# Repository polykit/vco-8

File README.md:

# Polykit Octo VCO aka VCO-8

This repository contains Kicad schematics and PCB layout for an octo 1V/oct VCO. It is based on [this design](https://github.com/polykit/vco-1).

Here you can listen to some short examples how it sounds: [example 1](https://soundcloud.com/polykit/polykit-octo-vco) [example 2](https://soundcloud.com/polykit/polykit-oxcto-vco-2)

# Building instructions

Building it is really straight forward. I suggest starting with components with the lowest height, eg. all SMD components, all diodes, all resistors and so on. Put all of one kind in place at the same time, eg. all 100k resistors. This helps to reduce problems while building it. If you want to try it out it is maybe a good idea to build the [single VCO](https://github.com/polykit/vco-1) version first.

You need either a pair of matched 2N3904s or one BC847BS transistor pair in a SMD package per VCO. I have very good tracking results with the BC847BS and not so good results with the 2N3904s. But maybe this is because of my poor matching. Bend the legs of the NTCs so that they are as close as possbile to the transistors.

## Powering

There are two powering options. First is 16-pin Eurorack with +12V, -12V and +5V. Second one is a 10-pin Eurorack with +12V and -12V and an additional TL431 for precise +5V supply. Make sure to put a jumper to `5V_ALT` and leave out `R3` if you opted for the latter. There is a testpoint `TP` where you can measure while adjusting `TRIM_5V_ALT` to +5.00V. I recommend the second option because of it's precision.

## Tuning

Use the power supply that you are going to use later on for tuning. Otherwise you might need to tune it again. I used a tuning device for this but also a tuning app for your mobile will work just fine. This is how I tuned the oscillators:

* Turn it on and wait at least 15 minutes before you start tuning
* Tune all oscillators roughly to a base note, eg. `C4`. Do this by applying the correct CV input and adjusting the offset trim pot.
* Next is to get the right scale. Start with the first oscillator and adjust scale until you have the correct interval between two notes, eg. your base note `C4` and `D4`. While changing scale overall tuning will change, so go back to your base note from time to time by adjusting the offset. When your are quite close to the correct scale fine tune it for a whole ocatve, eg. using notes `C4` and `C5`. Proceed with the next oscillator.
* Start again with the first oscillator until everything is in tune. Usually you only need to adjust offset for this.

## Tweaks

* Use ferrite beads or just jumpers instead of the 10R resistors for R3, R4 and R5. There is a significant voltage drop over the resistors leading to a lower peak-to-peak amplitude.
* Use 22µ polarized caps instead of 1µ non-polarized ones. The positive side (+) of the cap is torwards the op-amp and negative (-) to the output. I had the impression that it gives you a nicer ramp signal on the output.

## BOM

|Designator|Quantity                                                                                                                                                                                                           |Designation|
|----------|-------------------------------------------------------------------------------------------------------------------------------------------------------------------------------------------------------------------|-----------|
|U1        |1                                                                                                                                                                                                                  |TL431LP*** |
|TRIM_5V_ALT, OFFSET8, OFFSET7, OFFSET6, OFFSET5, OFFSET4, OFFSET3, OFFSET2, OFFSET1|9                                                                                                                                                                                                                  |100k       |
|R197, R36, R180, R156, R132, R108, R84, R60, R12|9                                                                                                                                                                                                                  |47k        |
|R196, R182, R158, R134, R110, R86, R62, R38, R14|9                                                                                                                                                                                                                  |270        |
|C16, C21, C58, C56, C51, C49, C44, C42, C37, C35, C30, C28, C14, C2, C5, C3, C23, C7, C9|19                                                                                                                                                                                                                 |100n       |
|C22, C57, C50, C43, C36, C29, C15, C8|8                                                                                                                                                                                                                  |1n         |
|R50, R195, R194, R171, R170, R147, R146, R123, R122, R99, R98, R75, R74, R51, R27, R26|16                                                                                                                                                                                                                 |1k         |
|R33, R177, R153, R129, R105, R81, R57, R9|8                                                                                                                                                                                                                  |4k7 NTC    |
|T16, T15, T14, T13, T12, T11, T10, T9, T8, T7, T6, T5, T4, T3, T1, T2|16                                                                                                                                                                                                                 |2N3904*    |
|SCALE8, SCALE7, SCALE6, SCALE5, SCALE4, SCALE3, SCALE2, SCALE1|8                                                                                                                                                                                                                  |100        |
|R193, R184, R175, R174, R173, R172, R169, R160, R151, R150, R149, R148, R145, R136, R127, R126, R125, R124, R121, R112, R103, R102, R101, R100, R97, R88, R79, R78, R77, R76, R73, R64, R55, R31, R30, R54, R53, R52, R49, R40, R29, R28, R6, R7, R2, R16, R1, R25|48                                                                                                                                                                                                                 |100k       |
|R192, R186, R176, R168, R162, R152, R144, R138, R128, R120, R114, R104, R96, R90, R80, R72, R66, R56, R32, R48, R42, R24, R8, R18|24                                                                                                                                                                                                                 |4k7        |
|R191, R189, R187, R167, R165, R163, R143, R141, R139, R119, R117, R115, R95, R93, R91, R71, R69, R67, R47, R45, R43, R19, R21, R23|24                                                                                                                                                                                                                 |10k        |
|R190, R166, R142, R118, R94, R70, R46, R22|8                                                                                                                                                                                                                  |2k         |
|R188, R164, R140, R116, R92, R68, R44, R20|8                                                                                                                                                                                                                  |1k8        |
|R185, R161, R137, R113, R89, R65, R41, R17|8                                                                                                                                                                                                                  |470k       |
|R183, R159, R135, R111, R87, R63, R39, R15|8                                                                                                                                                                                                                  |180k       |
|R181, R157, R133, R109, R85, R61, R37, R13|8                                                                                                                                                                                                                  |1M         |
|R179, R155, R131, R107, R83, R59, R35, R11|8                                                                                                                                                                                                                  |100*       |
|R178, R154, R130, R106, R82, R58, R34, R10|8                                                                                                                                                                                                                  |2k2        |
|Q16, Q14, Q12, Q10, Q8, Q6, Q4, Q2|8                                                                                                                                                                                                                  |BS170      |
|Q15, Q13, Q11, Q9, Q7, Q5, Q3, Q1|8                                                                                                                                                                                                                  |BC847BS*   |
|IC16, IC14, IC12, IC10, IC8, IC6, IC2, IC4|8                                                                                                                                                                                                                  |TL072P     |
|IC15, IC13, IC11, IC9, IC7, IC5, IC1, IC3|8                                                                                                                                                                                                                  |TL074P     |
|D16, D15, D14, D13, D12, D11, D10, D9, D8, D7, D6, D5, D4, D3, D2, D1|16                                                                                                                                                                                                                 |1N4148     |
|C62, C55, C48, C41, C34, C27, C20, C13|8                                                                                                                                                                                                                  |10n        |
|C61, C54, C47, C40, C33, C19, C26, C12|8                                                                                                                                                                                                                  |1µ**         |
|C60, C53, C46, C39, C32, C18, C25, C11|8                                                                                                                                                                                                                  |100p**       |
|C59, C52, C45, C38, C31, C17, C24, C10|8                                                                                                                                                                                                                  |1n**       |
|C6, C4, C1  |3                                                                                                                                                                                                                  |10µ polarized       |
|R4, R5, R3  |3                                                                                                                                                                                                                  |10         |
|PWR1      |1                                                                                                                                                                                                                  |ML16 or ML10***|                                                                                           

\* Use either matched pairs of 2N3904s or BC847BS dual transistors. Use 120R instead of 100R for R179, R155, R131, R107, R83, R59, R35 and R11 when you are going for the 2N3904s.

\** Use polypropylene or similar caps

\*** See powering options. Leave out U1, R196, R197 and TRIM_5V_ALT if you opted for 16-pin Eurorack supply with +5V in place.

# References

https://github.com/polykit/vco-1

https://www.diodes.com/assets/Datasheets/ds30222.pdf

https://www.ti.com/lit/ds/symlink/tl431.pdf

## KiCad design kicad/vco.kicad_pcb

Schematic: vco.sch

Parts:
C1, C4, C6: 47µ; E2,5-5
C2, C3, C5: 100n; C050-030X075
PWR1: ML16
R3, R4, R5: 10; 0207_7
R196: 270; 0207_7
R197: 47k; 0207_7
TP1: Conn_01x01; 1X01
TRIM_5V1: 100k; S64YW
U1: TL431LP; TO-92_Inline

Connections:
5V_ALT: R196.2, R197.1, TP1.1, U1.3 (K); also elsewhere on the board
+5V: C1.+, C3.2, R3.1; also elsewhere on the board
+12V: C5.2, C6.+, R4.1, R196.1; also elsewhere on the board
-12V: C2.2, C4.-, R5.1; also elsewhere on the board
GND: C1.-, C2.1, C3.1, C4.+, C5.1, C6.-, PWR1.3, PWR1.4, PWR1.5, PWR1.6, PWR1.7, PWR1.8, TRIM_5V1.E, TRIM_5V1.S, U1.2 (A); also elsewhere on the board
unnamed: PWR1.1, PWR1.2, R5.2
unnamed: PWR1.9, PWR1.10, R4.2
unnamed: PWR1.11, PWR1.12, R3.2
unnamed: R197.2, TRIM_5V1.A, U1.1 (REF)

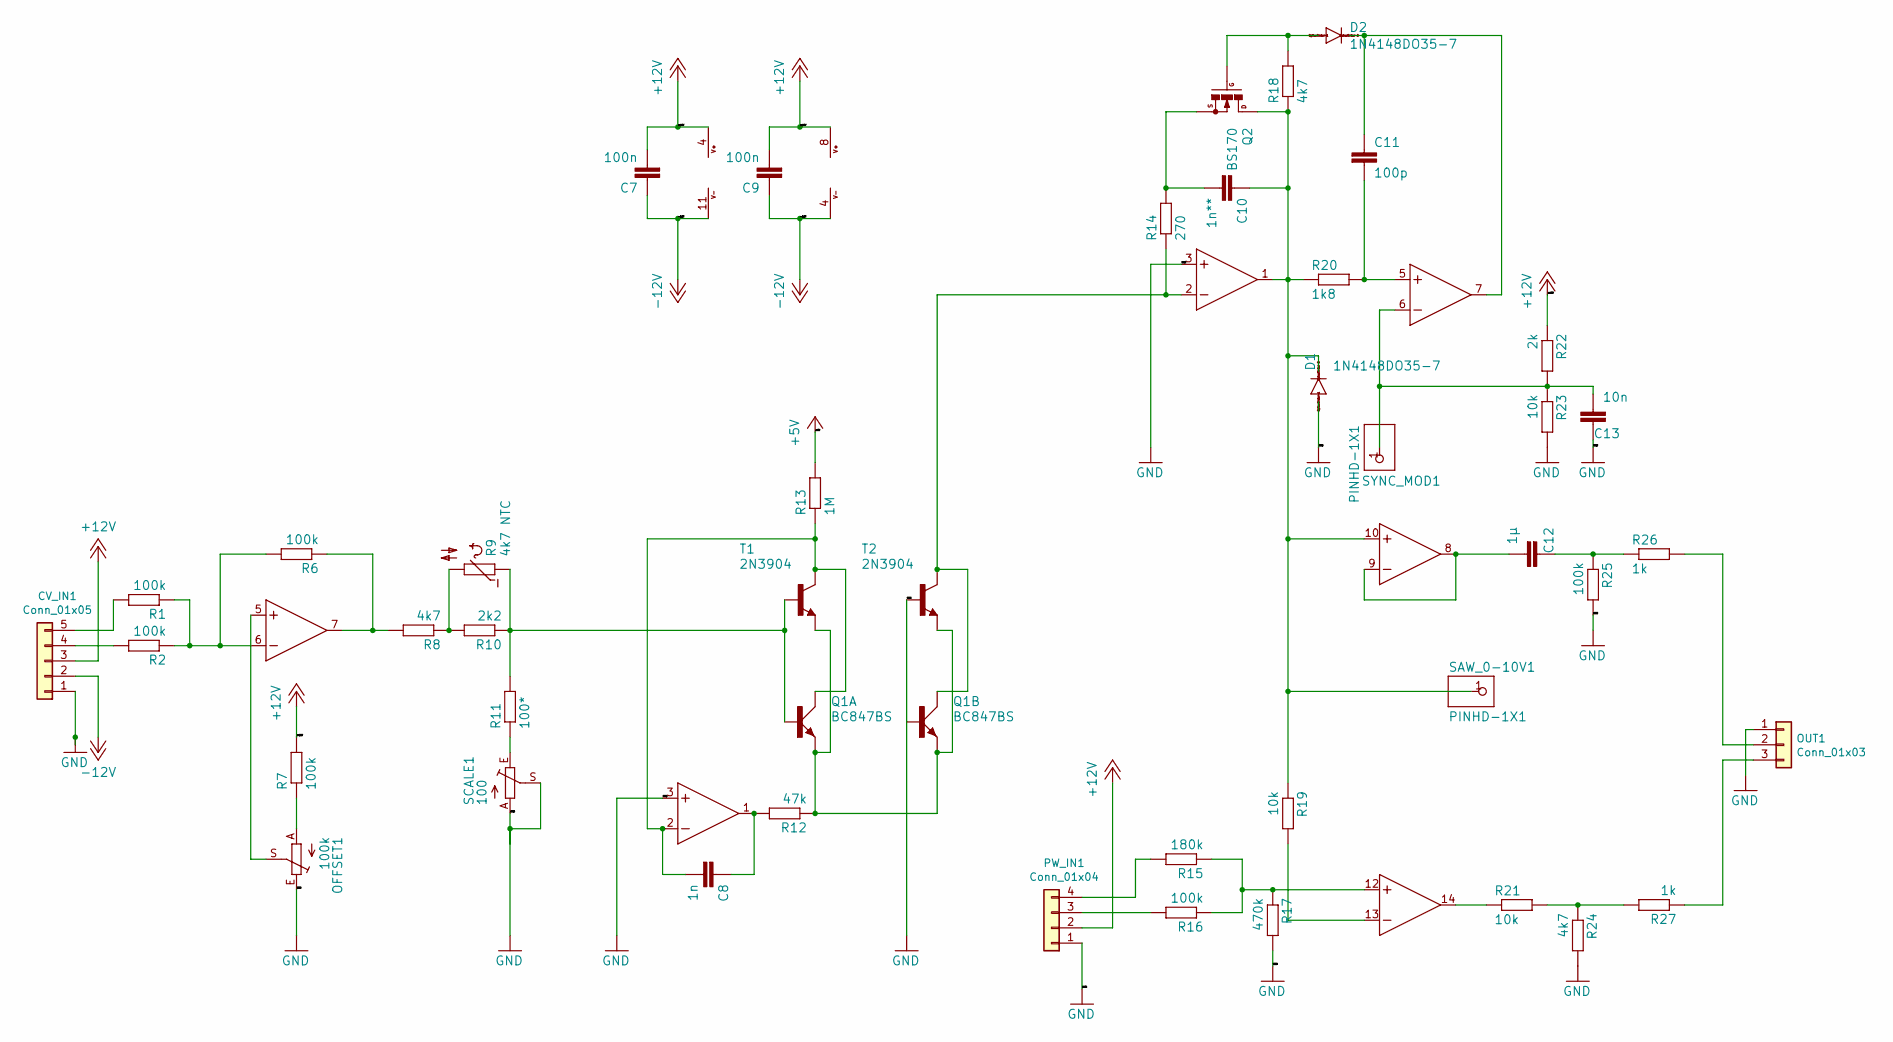
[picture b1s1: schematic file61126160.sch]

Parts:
C7, C9: 100n; C050-030X075
C8: 1n; C050-024X044
C10: 1n**; C050-030X075
C11: 100p; C050-030X075
C12: 1µ; C050-030X075
C13: 10n; C050-030X075
CV_IN1: Conn_01x05; Molex_KK-254_AE-6410-05A_1x05_P2.54mm_Vertical
D1, D2: 1N4148DO35-7; DO35-7
IC1: TL074P; DIL14
IC2: TL072P; DIL08
OFFSET1: 100k; S64YW
OUT1: Conn_01x03; Molex_KK-254_AE-6410-03A_1x03_P2.54mm_Vertical
PW_IN1: Conn_01x04; Molex_KK-254_AE-6410-04A_1x04_P2.54mm_Vertical
Q1: BC847BS; SOT363_PHILIPS
Q2: BS170; SOT54E
R1, R2, R6, R7, R16, R25: 100k; 0207_7
R8, R18, R24: 4k7; 0207_7
R9: 4k7 NTC; P640
R10: 2k2; 0207_7
R11: 100*; 0207_7
R12: 47k; 0207_7
R13: 1M; 0207_7
R14: 270; 0207_7
R15: 180k; 0207_7
R17: 470k; 0207_7
R19, R21, R23: 10k; 0207_7
R20: 1k8; 0207_7
R22: 2k; 0207_7
R26, R27: 1k; 0207_7
SAW_0-10V1: PINHD-1X1; 1X01
SCALE1: 100; S64YW
SYNC_MOD1: PINHD-1X1; 1X01
T1, T2: 2N3904; TO92

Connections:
+5V: R13.2; also elsewhere on the board
+12V: C7.2, C9.2, CV_IN1.3, IC1.4 (V+), IC2.8 (V+), PW_IN1.2, R7.2, R22.1; also elsewhere on the board
-12V: C7.1, C9.1, CV_IN1.2, IC1.11 (V-), IC2.4 (V-); also elsewhere on the board
GND: C13.1, CV_IN1.1, D1.A, IC1.3 (+IN), IC2.3 (+IN), OFFSET1.E, OUT1.1, PW_IN1.1, Q1.5 (B), R17.2, R23.2, R24.2, R25.2, SCALE1.A, SCALE1.S, T2.2 (B); also elsewhere on the board
unnamed: C8.1, IC1.1 (OUT), R12.2
unnamed: C8.2, IC1.2 (-IN), Q1.6 (C), R13.1, T1.1 (C)
unnamed: C10.1, D1.C, IC1.10 (+IN), IC2.1 (OUT), Q2.D, R18.1, R19.1, R20.1, SAW_0-10V1.1
unnamed: C10.2, Q2.S, R14.2
unnamed: C11.1, D2.C, IC2.7 (OUT)
unnamed: C11.2, IC2.5 (+IN), R20.2
unnamed: C12.1, R25.1, R26.1
unnamed: C12.2, IC1.8 (OUT), IC1.9 (-IN)
unnamed: C13.2, IC2.6 (-IN), R22.2, R23.1, SYNC_MOD1.1
unnamed: CV_IN1.4, R2.2
unnamed: CV_IN1.5, R1.2
unnamed: D2.A, Q2.G, R18.2
unnamed: IC1.5 (+IN), OFFSET1.S
unnamed: IC1.6 (-IN), R1.1, R2.1, R6.2
unnamed: IC1.7 (OUT), R6.1, R8.2
unnamed: IC1.12 (+IN), R15.1, R16.1, R17.1
unnamed: IC1.13 (-IN), R19.2
unnamed: IC1.14 (OUT), R21.1
unnamed: IC2.2 (-IN), Q1.3 (C), R14.1, T2.1 (C)
unnamed: OFFSET1.A, R7.1
unnamed: OUT1.2, R26.2
unnamed: OUT1.3, R27.1
unnamed: PW_IN1.3, R16.2
unnamed: PW_IN1.4, R15.2
unnamed: Q1.1 (E), Q1.4 (E), R12.1, T1.3 (E), T2.3 (E)
unnamed: Q1.2 (B), R9.1, R10.1, R11.2, T1.2 (B)
unnamed: R8.1, R9.2, R10.2
unnamed: R11.1, SCALE1.E
unnamed: R21.2, R24.1, R27.2

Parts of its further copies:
C14, C16, C21, C23, C28, C30, C35, C37, C42, C44, C49, C51, C56, C58: 100n; C050-030X075
C15, C29, C36, C43, C50, C57: 1n; C050-024X044
C17, C24, C31, C38, C45, C52, C59: 1n**; C050-030X075
C18, C25, C32, C39, C46, C53, C60: 100p; C050-030X075
C19, C33, C40, C47, C54, C61: 1µ; C050-030X075
C27, C34, C41, C48, C55, C62: 10n; C050-030X075
CV_IN2, CV_IN3, CV_IN4, CV_IN5, CV_IN6, CV_IN7, CV_IN8: Conn_01x05; Molex_KK-254_AE-6410-05A_1x05_P2.54mm_Vertical
D3, D4, D5, D6, D7, D8, D9, D10, D11, D12, D13, D14, D15, D16: 1N4148DO35-7; DO35-7
IC3, IC5, IC7, IC9, IC11, IC13, IC15: TL074P; DIL14
IC4, IC6, IC8, IC10, IC12, IC14, IC16: TL072P; DIL08
OFFSET2, OFFSET3, OFFSET4, OFFSET5, OFFSET6, OFFSET7, OFFSET8: 100k; S64YW
OUT2, OUT3, OUT4, OUT5, OUT6, OUT7, OUT8: Conn_01x03; Molex_KK-254_AE-6410-03A_1x03_P2.54mm_Vertical
PW_IN2, PW_IN3, PW_IN4, PW_IN5, PW_IN6, PW_IN7, PW_IN8: Conn_01x04; Molex_KK-254_AE-6410-04A_1x04_P2.54mm_Vertical
Q3, Q5, Q7, Q9, Q11, Q13, Q15: BC847BS; SOT363_PHILIPS
Q4, Q6, Q8, Q10, Q12, Q14, Q16: BS170; SOT54E
R28, R29, R30, R31, R52, R53, R55, R64, R73, R76, R77, R78, R79, R88, R97, R100, R101, R102, R103, R112, R121, R124, R125, R126, R127, R136, R145, R148, R149, R150, R151, R160, R169, R172, R173, R174, R175, R184, R193: 100k; 0207_7
R32, R56, R66, R72, R80, R90, R96, R104, R114, R120, R128, R138, R144, R152, R162, R168, R176, R186, R192: 4k7; 0207_7
R33, R57, R81, R105, R129, R153, R177: 4k7 NTC; P640
R34, R58, R82, R106, R130, R154, R178: 2k2; 0207_7
R37, R61, R85, R109, R133, R157, R181: 1M; 0207_7
R38, R62, R86, R110, R134, R158, R182: 270; 0207_7
R39, R63, R87, R111, R135, R159, R183: 180k; 0207_7
R43, R45, R67, R69, R71, R91, R93, R95, R115, R117, R119, R139, R141, R143, R163, R165, R167, R187, R189, R191: 10k; 0207_7
R44, R68, R92, R116, R140, R164, R188: 1k8; 0207_7
R50, R51, R74, R75, R98, R99, R122, R123, R146, R147, R170, R171, R194, R195: 1k; 0207_7
R59, R83, R107, R131, R155, R179: 100*; 0207_7
R60, R84, R108, R132, R156, R180: 47k; 0207_7
R65, R89, R113, R137, R161, R185: 470k; 0207_7
R70, R94, R118, R142, R166, R190: 2k; 0207_7
SAW_0-10V2, SAW_0-10V3, SAW_0-10V4, SAW_0-10V5, SAW_0-10V6, SAW_0-10V7, SAW_0-10V8: PINHD-1X1; 1X01
SCALE2, SCALE3, SCALE4, SCALE5, SCALE6, SCALE7, SCALE8: 100; S64YW
SYNC_MOD2, SYNC_MOD3, SYNC_MOD4, SYNC_MOD5, SYNC_MOD6, SYNC_MOD7, SYNC_MOD8: PINHD-1X1; 1X01
T3, T4, T5, T6, T7, T8, T9, T10, T11, T12, T13, T14, T15, T16: 2N3904; TO92

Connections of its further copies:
+5V: R37.2, R61.2, R85.2, R109.2, R133.2, R157.2, R181.2; also elsewhere on the board
+12V: C14.2, C16.2, C21.2, C23.2, C28.2, C30.2, C35.2, C37.2, C42.2, C44.2, C49.2, C51.2, C56.2, C58.2, CV_IN2.3, CV_IN3.3, CV_IN4.3, CV_IN5.3, CV_IN6.3, CV_IN7.3, CV_IN8.3, IC3.4 (V+), IC4.8 (V+), IC5.4 (V+), IC6.8 (V+), IC7.4 (V+), IC8.8 (V+), IC9.4 (V+), IC10.8 (V+), IC11.4 (V+), IC12.8 (V+), IC13.4 (V+), IC14.8 (V+), IC15.4 (V+), IC16.8 (V+), PW_IN2.2, PW_IN3.2, PW_IN4.2, PW_IN5.2, PW_IN6.2, PW_IN7.2, PW_IN8.2, R31.2, R55.2, R70.1, R79.2, R94.1, R103.2, R118.1, R127.2, R142.1, R151.2, R166.1, R175.2, R190.1; also elsewhere on the board
-12V: C14.1, C16.1, C21.1, C23.1, C28.1, C30.1, C35.1, C37.1, C42.1, C44.1, C49.1, C51.1, C56.1, C58.1, CV_IN2.2, CV_IN3.2, CV_IN4.2, CV_IN5.2, CV_IN6.2, CV_IN7.2, CV_IN8.2, IC3.11 (V-), IC4.4 (V-), IC5.11 (V-), IC6.4 (V-), IC7.11 (V-), IC8.4 (V-), IC9.11 (V-), IC10.4 (V-), IC11.11 (V-), IC12.4 (V-), IC13.11 (V-), IC14.4 (V-), IC15.11 (V-), IC16.4 (V-); also elsewhere on the board
GND: C27.1, C34.1, C41.1, C48.1, C55.1, C62.1, CV_IN2.1, CV_IN3.1, CV_IN4.1, CV_IN5.1, CV_IN6.1, CV_IN7.1, CV_IN8.1, D3.A, D5.A, D7.A, D9.A, D11.A, D13.A, D15.A, IC3.3 (+IN), IC4.3 (+IN), IC5.3 (+IN), IC6.3 (+IN), IC7.3 (+IN), IC8.3 (+IN), IC9.3 (+IN), IC10.3 (+IN), IC11.3 (+IN), IC12.3 (+IN), IC13.3 (+IN), IC14.3 (+IN), IC15.3 (+IN), IC16.3 (+IN), OFFSET2.E, OFFSET3.E, OFFSET4.E, OFFSET5.E, OFFSET6.E, OFFSET7.E, OFFSET8.E, OUT2.1, OUT3.1, OUT4.1, OUT5.1, OUT6.1, OUT7.1, OUT8.1, PW_IN2.1, PW_IN3.1, PW_IN4.1, PW_IN5.1, PW_IN6.1, PW_IN7.1, PW_IN8.1, Q3.5 (B), Q5.5 (B), Q7.5 (B), Q9.5 (B), Q11.5 (B), Q13.5 (B), Q15.5 (B), R65.2, R71.2, R72.2, R73.2, R89.2, R95.2, R96.2, R97.2, R113.2, R119.2, R120.2, R121.2, R137.2, R143.2, R144.2, R145.2, R161.2, R167.2, R168.2, R169.2, R185.2, R191.2, R192.2, R193.2, SCALE2.A, SCALE2.S, SCALE3.A, SCALE3.S, SCALE4.A, SCALE4.S, SCALE5.A, SCALE5.S, SCALE6.A, SCALE6.S, SCALE7.A, SCALE7.S, SCALE8.A, SCALE8.S, T4.2 (B), T6.2 (B), T8.2 (B), T10.2 (B), T12.2 (B), T14.2 (B), T16.2 (B); also elsewhere on the board
unnamed 14: C15.1, IC3.1 (OUT); also elsewhere on the board
unnamed: C15.2, IC3.2 (-IN), Q3.6 (C), R37.1, T3.1 (C)
unnamed 16: C17.1, D3.C, IC3.10 (+IN), IC4.1 (OUT), Q4.D, R43.1, R44.1, SAW_0-10V2.1; also elsewhere on the board
unnamed: C17.2, Q4.S, R38.2
unnamed: C18.1, D4.C, IC4.7 (OUT)
unnamed: C18.2, IC4.5 (+IN), R44.2
unnamed 20: C19.1, R50.1; also elsewhere on the board
unnamed: C19.2, IC3.8 (OUT), IC3.9 (-IN)
unnamed 22: IC4.6 (-IN), SYNC_MOD2.1; also elsewhere on the board
unnamed 23: IC5.1 (OUT), R60.2; also elsewhere on the board
unnamed 24: IC5.2 (-IN), Q5.6 (C), R61.1, T5.1 (C); also elsewhere on the board
unnamed: C24.1, D5.C, IC5.10 (+IN), IC6.1 (OUT), Q6.D, R66.1, R67.1, R68.1, SAW_0-10V3.1
unnamed: C24.2, Q6.S, R62.2
unnamed: C25.1, D6.C, IC6.7 (OUT)
unnamed: C25.2, IC6.5 (+IN), R68.2
unnamed 29: R73.1, R74.1; also elsewhere on the board
unnamed 30: IC5.8 (OUT), IC5.9 (-IN); also elsewhere on the board
unnamed: C27.2, IC6.6 (-IN), R70.2, R71.1, SYNC_MOD3.1
unnamed: C29.1, IC7.1 (OUT), R84.2
unnamed: C29.2, IC7.2 (-IN), Q7.6 (C), R85.1, T7.1 (C)
unnamed: C31.1, D7.C, IC7.10 (+IN), IC8.1 (OUT), Q8.D, R90.1, R91.1, R92.1, SAW_0-10V4.1
unnamed: C31.2, Q8.S, R86.2
unnamed: C32.1, D8.C, IC8.7 (OUT)
unnamed: C32.2, IC8.5 (+IN), R92.2
unnamed: C33.1, R97.1, R98.1
unnamed: C33.2, IC7.8 (OUT), IC7.9 (-IN)
unnamed: C34.2, IC8.6 (-IN), R94.2, R95.1, SYNC_MOD4.1
unnamed: C36.1, IC9.1 (OUT), R108.2
unnamed: C36.2, IC9.2 (-IN), Q9.6 (C), R109.1, T9.1 (C)
unnamed: C38.1, D9.C, IC9.10 (+IN), IC10.1 (OUT), Q10.D, R114.1, R115.1, R116.1, SAW_0-10V5.1
unnamed: C38.2, Q10.S, R110.2
unnamed: C39.1, D10.C, IC10.7 (OUT)
unnamed: C39.2, IC10.5 (+IN), R116.2
unnamed: C40.1, R121.1, R122.1
unnamed: C40.2, IC9.8 (OUT), IC9.9 (-IN)
unnamed: C41.2, IC10.6 (-IN), R118.2, R119.1, SYNC_MOD5.1
unnamed: C43.1, IC11.1 (OUT), R132.2
unnamed: C43.2, IC11.2 (-IN), Q11.6 (C), R133.1, T11.1 (C)
unnamed: C45.1, D11.C, IC11.10 (+IN), IC12.1 (OUT), Q12.D, R138.1, R139.1, R140.1, SAW_0-10V6.1
unnamed: C45.2, Q12.S, R134.2
unnamed: C46.1, D12.C, IC12.7 (OUT)
unnamed: C46.2, IC12.5 (+IN), R140.2
unnamed: C47.1, R145.1, R146.1
unnamed: C47.2, IC11.8 (OUT), IC11.9 (-IN)
unnamed: C48.2, IC12.6 (-IN), R142.2, R143.1, SYNC_MOD6.1
unnamed: C50.1, IC13.1 (OUT), R156.2
unnamed: C50.2, IC13.2 (-IN), Q13.6 (C), R157.1, T13.1 (C)
unnamed: C52.1, D13.C, IC13.10 (+IN), IC14.1 (OUT), Q14.D, R162.1, R163.1, R164.1, SAW_0-10V7.1
unnamed: C52.2, Q14.S, R158.2
unnamed: C53.1, D14.C, IC14.7 (OUT)
unnamed: C53.2, IC14.5 (+IN), R164.2
unnamed: C54.1, R169.1, R170.1
unnamed: C54.2, IC13.8 (OUT), IC13.9 (-IN)
unnamed: C55.2, IC14.6 (-IN), R166.2, R167.1, SYNC_MOD7.1
unnamed: C57.1, IC15.1 (OUT), R180.2
unnamed: C57.2, IC15.2 (-IN), Q15.6 (C), R181.1, T15.1 (C)
unnamed: C59.1, D15.C, IC15.10 (+IN), IC16.1 (OUT), Q16.D, R186.1, R187.1, R188.1, SAW_0-10V8.1
unnamed: C59.2, Q16.S, R182.2
unnamed: C60.1, D16.C, IC16.7 (OUT)
unnamed: C60.2, IC16.5 (+IN), R188.2
unnamed: C61.1, R193.1, R194.1
unnamed: C61.2, IC15.8 (OUT), IC15.9 (-IN)
unnamed: C62.2, IC16.6 (-IN), R190.2, R191.1, SYNC_MOD8.1
unnamed: CV_IN2.4, R29.2
unnamed: CV_IN2.5, R28.2
unnamed: CV_IN3.4, R53.2
unnamed: CV_IN3.5, R52.2
unnamed: CV_IN4.4, R77.2
unnamed: CV_IN4.5, R76.2
unnamed: CV_IN5.4, R101.2
unnamed: CV_IN5.5, R100.2
unnamed: CV_IN6.4, R125.2
unnamed: CV_IN6.5, R124.2
unnamed: CV_IN7.4, R149.2
unnamed: CV_IN7.5, R148.2
unnamed: CV_IN8.4, R173.2
unnamed: CV_IN8.5, R172.2
unnamed 94: D4.A, Q4.G; also elsewhere on the board
unnamed: D6.A, Q6.G, R66.2
unnamed: D8.A, Q8.G, R90.2
unnamed: D10.A, Q10.G, R114.2
unnamed: D12.A, Q12.G, R138.2
unnamed: D14.A, Q14.G, R162.2
unnamed: D16.A, Q16.G, R186.2
unnamed: IC3.5 (+IN), OFFSET2.S
unnamed: IC3.6 (-IN), R28.1, R29.1, R30.2
unnamed: IC3.7 (OUT), R30.1, R32.2
unnamed 111: IC3.12 (+IN), R39.1; also elsewhere on the board
unnamed: IC3.13 (-IN), R43.2
unnamed: IC3.14 (OUT), R45.1
unnamed: IC4.2 (-IN), Q3.3 (C), R38.1, T4.1 (C)
unnamed: IC5.5 (+IN), OFFSET3.S
unnamed 116: IC5.6 (-IN), R52.1, R53.1; also elsewhere on the board
unnamed 117: IC5.7 (OUT), R56.2; also elsewhere on the board
unnamed: IC5.12 (+IN), R63.1, R64.1, R65.1
unnamed: IC5.13 (-IN), R67.2
unnamed: IC5.14 (OUT), R69.1
unnamed: IC6.2 (-IN), Q5.3 (C), R62.1, T6.1 (C)
unnamed: IC7.5 (+IN), OFFSET4.S
unnamed: IC7.6 (-IN), R76.1, R77.1, R78.2
unnamed: IC7.7 (OUT), R78.1, R80.2
unnamed: IC7.12 (+IN), R87.1, R88.1, R89.1
unnamed: IC7.13 (-IN), R91.2
unnamed: IC7.14 (OUT), R93.1
unnamed: IC8.2 (-IN), Q7.3 (C), R86.1, T8.1 (C)
unnamed: IC9.5 (+IN), OFFSET5.S
unnamed: IC9.6 (-IN), R100.1, R101.1, R102.2
unnamed: IC9.7 (OUT), R102.1, R104.2
unnamed: IC9.12 (+IN), R111.1, R112.1, R113.1
unnamed: IC9.13 (-IN), R115.2
unnamed: IC9.14 (OUT), R117.1
unnamed: IC10.2 (-IN), Q9.3 (C), R110.1, T10.1 (C)
unnamed: IC11.5 (+IN), OFFSET6.S
unnamed: IC11.6 (-IN), R124.1, R125.1, R126.2
unnamed: IC11.7 (OUT), R126.1, R128.2
unnamed: IC11.12 (+IN), R135.1, R136.1, R137.1
unnamed: IC11.13 (-IN), R139.2
unnamed: IC11.14 (OUT), R141.1
unnamed: IC12.2 (-IN), Q11.3 (C), R134.1, T12.1 (C)
unnamed: IC13.5 (+IN), OFFSET7.S
unnamed: IC13.6 (-IN), R148.1, R149.1, R150.2
unnamed: IC13.7 (OUT), R150.1, R152.2
unnamed: IC13.12 (+IN), R159.1, R160.1, R161.1
unnamed: IC13.13 (-IN), R163.2
unnamed: IC13.14 (OUT), R165.1
unnamed: IC14.2 (-IN), Q13.3 (C), R158.1, T14.1 (C)
unnamed: IC15.5 (+IN), OFFSET8.S
unnamed: IC15.6 (-IN), R172.1, R173.1, R174.2
unnamed: IC15.7 (OUT), R174.1, R176.2
unnamed: IC15.12 (+IN), R183.1, R184.1, R185.1
unnamed: IC15.13 (-IN), R187.2
unnamed: IC15.14 (OUT), R189.1
unnamed: IC16.2 (-IN), Q15.3 (C), R182.1, T16.1 (C)
unnamed: OFFSET2.A, R31.1
unnamed: OFFSET3.A, R55.1
unnamed: OFFSET4.A, R79.1
unnamed: OFFSET5.A, R103.1
unnamed: OFFSET6.A, R127.1
unnamed: OFFSET7.A, R151.1
unnamed: OFFSET8.A, R175.1
unnamed: OUT2.2, R50.2
unnamed: OUT2.3, R51.1
unnamed: OUT3.2, R74.2
unnamed: OUT3.3, R75.1
unnamed: OUT4.2, R98.2
unnamed: OUT4.3, R99.1
unnamed: OUT5.2, R122.2
unnamed: OUT5.3, R123.1
unnamed: OUT6.2, R146.2
unnamed: OUT6.3, R147.1
unnamed: OUT7.2, R170.2
unnamed: OUT7.3, R171.1
unnamed: OUT8.2, R194.2
unnamed: OUT8.3, R195.1
unnamed 190: PW_IN2.3; also elsewhere on the board
unnamed: PW_IN2.4, R39.2
unnamed: PW_IN3.3, R88.2
unnamed: PW_IN3.4, R87.2
unnamed: PW_IN4.3, R64.2
unnamed: PW_IN4.4, R63.2
unnamed: PW_IN5.3, R112.2
unnamed: PW_IN5.4, R111.2
unnamed: PW_IN6.3, R136.2
unnamed: PW_IN6.4, R135.2
unnamed: PW_IN7.3, R160.2
unnamed: PW_IN7.4, R159.2
unnamed: PW_IN8.3, R184.2
unnamed: PW_IN8.4, R183.2
unnamed 206: Q3.1 (E), Q3.4 (E), T3.3 (E), T4.3 (E); also elsewhere on the board
unnamed 207: Q3.2 (B), R33.1, R34.1, T3.2 (B); also elsewhere on the board
unnamed: Q5.1 (E), Q5.4 (E), R60.1, T5.3 (E), T6.3 (E)
unnamed: Q5.2 (B), R57.1, R58.1, R59.2, T5.2 (B)
unnamed: Q7.1 (E), Q7.4 (E), R84.1, T7.3 (E), T8.3 (E)
unnamed: Q7.2 (B), R81.1, R82.1, R83.2, T7.2 (B)
unnamed: Q9.1 (E), Q9.4 (E), R108.1, T9.3 (E), T10.3 (E)
unnamed: Q9.2 (B), R105.1, R106.1, R107.2, T9.2 (B)
unnamed: Q11.1 (E), Q11.4 (E), R132.1, T11.3 (E), T12.3 (E)
unnamed: Q11.2 (B), R129.1, R130.1, R131.2, T11.2 (B)
unnamed: Q13.1 (E), Q13.4 (E), R156.1, T13.3 (E), T14.3 (E)
unnamed: Q13.2 (B), R153.1, R154.1, R155.2, T13.2 (B)
unnamed: Q15.1 (E), Q15.4 (E), R180.1, T15.3 (E), T16.3 (E)
unnamed: Q15.2 (B), R177.1, R178.1, R179.2, T15.2 (B)
unnamed: R32.1, R33.2, R34.2
unnamed 224: SCALE2.E; also elsewhere on the board
unnamed 225: R45.2, R51.2; also elsewhere on the board
unnamed: R56.1, R57.2, R58.2
unnamed: R59.1, SCALE3.E
unnamed: R69.2, R72.1, R75.2
unnamed: R80.1, R81.2, R82.2
unnamed: R83.1, SCALE4.E
unnamed: R93.2, R96.1, R99.2
unnamed: R104.1, R105.2, R106.2
unnamed: R107.1, SCALE5.E
unnamed: R117.2, R120.1, R123.2
unnamed: R128.1, R129.2, R130.2
unnamed: R131.1, SCALE6.E
unnamed: R141.2, R144.1, R147.2
unnamed: R152.1, R153.2, R154.2
unnamed: R155.1, SCALE7.E
unnamed: R165.2, R168.1, R171.2
unnamed: R176.1, R177.2, R178.2
unnamed: R179.1, SCALE8.E
unnamed: R189.2, R192.1, R195.2

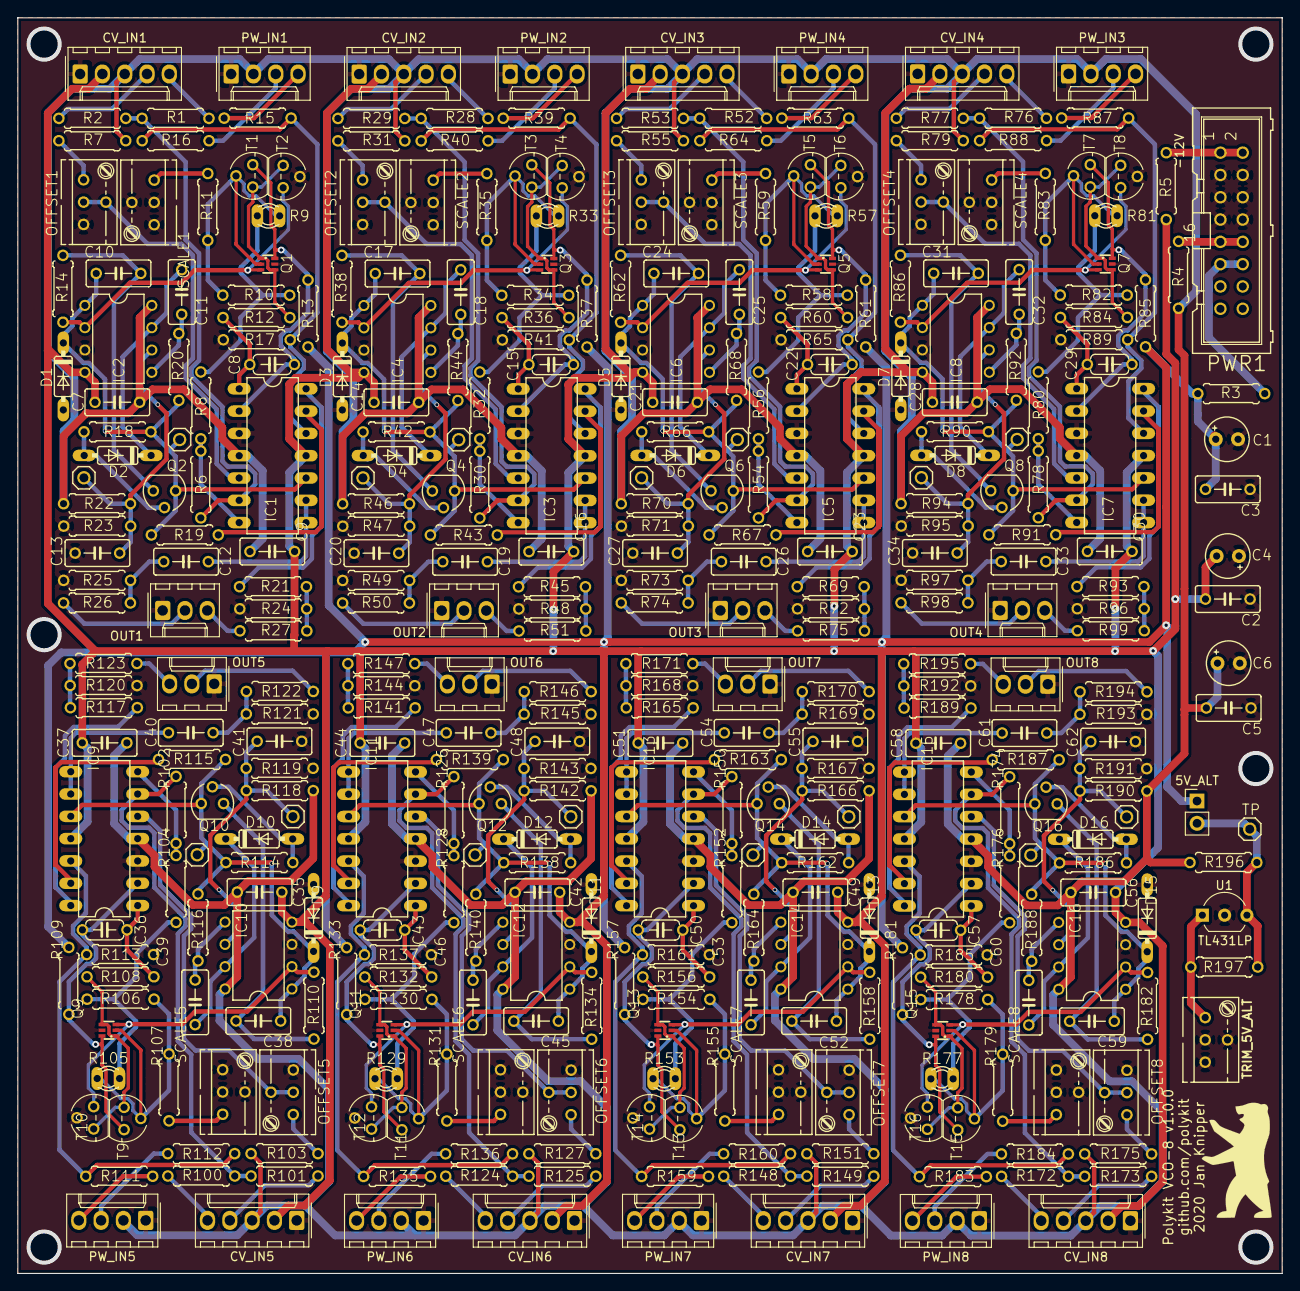
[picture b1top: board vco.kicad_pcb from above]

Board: 2 copper layers, 144.0 x 143.0 mm, 384 parts (0 on the bottom side), 241 nets.

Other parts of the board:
5V_ALT: PinHeader_1x02_P2.54mm_Vertical
C20: 10n; C050-030X075
C22: 1n; C050-024X044
C26: 1µ; C050-030X075
R35: 100*; 0207_7
R36: 47k; 0207_7
R40, R49, R54: 100k; 0207_7
R41: 470k; 0207_7
R42, R48: 4k7; 0207_7
R46: 2k; 0207_7
R47: 10k; 0207_7
TP: Conn_01x01; 1X01

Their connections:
5V_ALT: 5V_ALT.2, TP.1; also elsewhere on the board
+5V: 5V_ALT.1; also elsewhere on the board
+12V: R46.1; also elsewhere on the board
GND: C20.1, R41.2, R47.2, R48.2, R49.2; also elsewhere on the board
unnamed 14: R36.2; also elsewhere on the board
unnamed 16: R42.1; also elsewhere on the board
unnamed 20: R49.1; also elsewhere on the board
unnamed 22: C20.2, R46.2, R47.1; also elsewhere on the board
unnamed 23: C22.1; also elsewhere on the board
unnamed 24: C22.2; also elsewhere on the board
unnamed 29: C26.1; also elsewhere on the board
unnamed 30: C26.2; also elsewhere on the board
unnamed 94: R42.2; also elsewhere on the board
unnamed 111: R40.1, R41.1; also elsewhere on the board
unnamed 116: R54.2; also elsewhere on the board
unnamed 117: R54.1; also elsewhere on the board
unnamed 190: R40.2; also elsewhere on the board
unnamed 206: R36.1; also elsewhere on the board
unnamed 207: R35.2; also elsewhere on the board
unnamed 224: R35.1; also elsewhere on the board
unnamed 225: R48.1; also elsewhere on the board

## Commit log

2021-01-22 Initial import
2021-02-01 Added documentation
2021-02-02 Added tweaks
2021-02-13 Fix bom
